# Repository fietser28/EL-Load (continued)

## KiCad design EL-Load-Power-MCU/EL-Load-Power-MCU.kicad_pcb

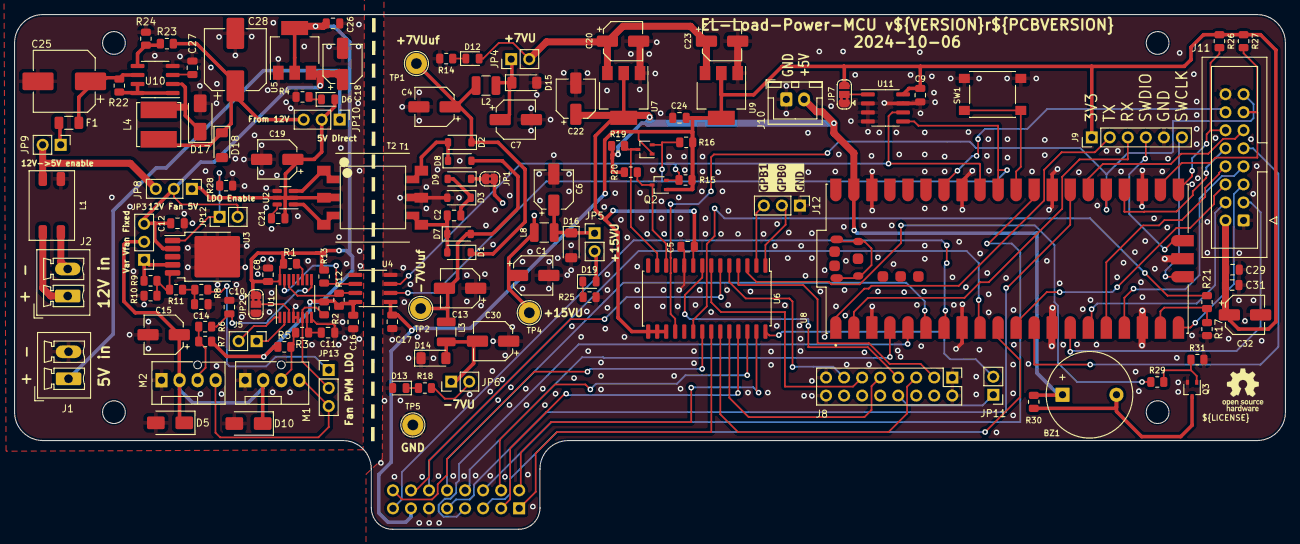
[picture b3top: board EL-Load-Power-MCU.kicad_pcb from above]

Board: 4 copper layers, 179.0 x 72.5 mm, 137 parts (1 on the bottom side), 108 nets.

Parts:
BZ1: Buzzer; Buzzer_12x9.5RM7.6
C1, C4, C6, C7, C13, C15, C18, C19, C20, C22, C23, C30, C32: 10u; CP_Elec_5x5.8
C2, C14, C29: 1u; C_0805_2012Metric
C5, C8, C9, C10, C11, C16, C17, C21, C31: 100n; C_0805_2012Metric
C12: 2.2u; C_0805_2012Metric
C24, C26: 10u; C_0805_2012Metric
C25, C28: 100u; CP_Elec_8x10.5
C27: 200p; C_0805_2012Metric
D1, D2, D3, D7, D8, D9: MBR0530; D_SOD-123
D5, D10, D17: SS14; D_SMA
D6, D12, D13, D19: LED; LED_0805_2012Metric
D14, D15: 16V; D_MiniMELF
D16: 20V; D_MiniMELF
D18: BZV55B5V6; D_MiniMELF
F1: 1A; Fuse_1206_3216Metric
H1, H2, H3, H4: MountingHole; MountingHole_3.2mm_M3_ISO14580
J1, J2: Conn_01x02; PhoenixContact_MCV_1,5_2-G-3.81_1x02_P3.81mm_Vertical
J5: PN sensor; PinHeader_1x02_P2.54mm_Vertical
J7, J8: PinHeader 2x08 P2.54mm; PinHeader_2x08_P2.54mm_Vertical
J9: SWD+UART header; PinHeader_1x06_P2.54mm_Vertical
J10: Power for serial interface; JST_XH_B2B-XH-A_1x02_P2.50mm_Vertical
J11: IDC-Header 2x08 P2.54mm; IDC-Header_2x08_P2.54mm_Vertical
J12: Conn_01x05_Pin; PinHeader_1x03_P2.54mm_Vertical
JP1: SolderJumper_2_Bridged; SolderJumper-2_P1.3mm_Bridged2Bar_RoundedPad1.0x1.5mm
JP2: I2C Address; SolderJumper-3_P1.3mm_Bridged2Bar12_RoundedPad1.0x1.5mm
JP3: Fan Volt/PWM; PinHeader_1x03_P2.54mm_Vertical
JP4, JP5, JP6, JP9: Jumper_2_Bridged; PinHeader_1x02_P2.54mm_Vertical
JP7: Jumper_3_Bridged12; SolderJumper-3_P1.3mm_Bridged2Bar12_RoundedPad1.0x1.5mm
JP8: Select Fan Voltage; PinHeader_1x03_P2.54mm_Vertical
JP10: Select 5V source; PinHeader_1x03_P2.54mm_Vertical
JP11: HW V3/V4; PinHeader_1x02_P2.54mm_Vertical
JP12: LDO En; PinHeader_1x02_P2.54mm_Vertical
JP13: PWM 2 LDO/PWM; PinHeader_1x03_P2.54mm_Vertical
L1: SRF0905-202Y; L_Bourns_SRF1260
L2, L3, L8: 10u; L_1210_3225Metric
L4: 100u / 300mA; L_Bourns_SRN6045TA
M1, M2: Fan_4pin; FanPinHeader_1x04_P2.54mm_Vertical
PCB1: Logo_Open_Hardware_Small; OSHW-Logo_5.7x6mm_SilkScreen
Q1, Q2, Q3: BSS138W; SOT-323_SC-70
R1, R2: 4k7; R_0805_2012Metric
R3, R6: 10; R_0805_2012Metric
R4, R14, R18, R21, R23, R28: 10k; R_0805_2012Metric
R5, R7, R8, R29, R30: 1k; R_0805_2012Metric
R9: 39k; R_0805_2012Metric
R10, R11, R24: 3k3; R_0805_2012Metric
R12, R13, R15, R16, R19, R20, R26, R27: 3k; R_0805_2012Metric
R17, R25, R31: 20k; R_0805_2012Metric
R22: 0.3; R_0805_2012Metric
SW1: Pico Reset; SW_Push_1P1T_NO_6x6mm_H9.5mm
T1: Wuerth_750315371; L_Wuerth_750315371
T2: Wuerth_750316031; L_Wuerth_750316031
TP1, TP2, TP4, TP5: TestPoint_Probe; TestPoint_Loop_D2.54mm_Drill1.5mm_Beaded
U1: MAX31760; QSOP-16_3.9x4.9mm_P0.635mm
U2: SN6505BDBV; SOT-23-6
U3: BD00FC0WFP-E2; TO-252-5_TabPin6
U4: Si8602AB; SOIC-8_3.9x4.9mm_P1.27mm
U5, U9: AMS1117-3.3; SOT-223-3_TabPin2
U6: MCP23017_SO; SOIC-28W_7.5x17.9mm_P1.27mm
U7: AZ1117-5.0; SOT-223-3_TabPin2
U8: SC0915; MODULE_SC0915
U10: MC34063AD; SOIC-8_3.9x4.9mm_P1.27mm
U11: 24C64; SOIC-8_3.9x4.9mm_P1.27mm
kibuzzard-66FFF99B: G***; kibuzzard-66FFF99B

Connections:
+3V3: C9.1, C17.2, C24.2, C29.1, C31.2, C32.1, J7.13, J9.1, J11.2, JP7.3 (B), Q1.1 (G), Q2.1 (G), R15.1, R16.1, R26.1, R27.1, U4.1 (AVDD), U9.2 (VO), U11.8 (VCC)
+3V3_ISO: C8.1, C16.2, C26.2, JP2.1 (A), R1.2, R2.1, R5.1, R7.1, R12.1, R13.1, U1.16 (VDD), U4.8 (BVDD), U5.2 (VO)
+5VD: BZ1.1 (-), C5.2, C22.1, J10.2, R19.1, R20.1, R30.1, U6.9 (VDD), U6.15 (A0), U6.16 (A1), U6.17 (A2), U7.2 (VO), U8.39 (VSYS)
+5V_ISO: C19.1, C21.2, D6.2 (A), JP8.1 (A), JP10.2 (C), T1.2 (N2-A), T2.2 (N2-A), U2.2 (VCC), U2.5 (EN)
+7VU: C20.1, C23.1, D12.2 (A), J8.4, J8.6, JP4.2 (B), U7.3 (VI), U9.3 (VI)
+12V_ISO: JP8.3 (B), JP9.2 (B), L1.3
+15VU: D19.2 (A), J8.10, JP5.2 (B)
+V_FANS: C12.1, C18.1, JP3.3 (B), JP8.2 (C), JP12.2 (B), U3.2 (Vcc), U5.3 (VI)
-7VU: J8.12, J8.14, JP6.2 (B), R18.2
/BLK: J11.7, U8.17 (GP13)
/CS1: J11.9, U8.12 (GP9)
/CS2: J11.10, U8.24 (GP18)
/DC: J11.6, U8.11 (GP8)
/Fan Controllers/Fan1PWM: JP13.3 (B), M1.4 (PWM), M2.4 (PWM)
/Fan Controllers/Fan1PWR: C15.1, D5.1 (K), D10.1 (K), JP3.2 (C), M1.2 (+), M2.2 (+)
/Fan Controllers/Fan1Tacho: M1.3 (Tacho), R3.2, R5.2
/Fan Controllers/Fan2Tacho: M2.3 (Tacho), R6.2, R7.2
/Fan Controllers/SCL_ISO: R13.2, U1.15 (SCL), U4.6 (BSCL)
/Fan Controllers/SDA_ISO: R12.2, U1.14 (SDA), U4.7 (BSDA)
/INT: J11.14, U8.34 (GP28)
/MCU/Buzzer: R29.1, U6.3 (GPB2)
/MCU/EL-ADC_CLK: J7.9, U8.27 (GP21)
/MCU/EL-ADC_CS: J7.6, U8.29 (GP22)
/MCU/EL-ADC_RDY: J7.5, U8.10 (GP7)
/MCU/EL-DAC1_CS: J7.12, U8.9 (GP6)
/MCU/EL-DAC2_CS: J7.15, U8.7 (GP5)
/MCU/EL-SPI_RX: J7.10, U8.6 (GP4)
/MCU/EL-SPI_SCK: J7.8, U8.4 (GP2)
/MCU/EL-SPI_TX: J7.7, U8.5 (GP3)
/MCU/HWGPIO_INT: R17.1, R21.2, U8.19 (GP14)
/MCU/HWIO_SCL: Q2.2 (S), R15.2, U4.3 (ASCL), U8.32 (GP27), U11.6 (SCL)
/MCU/HWIO_SDA: Q1.2 (S), R16.2, U4.2 (ASDA), U8.31 (GP26), U11.5 (SDA)
/MCU/HWProtEnable: J8.5, U6.23 (GPA2)
/MCU/OCPtriggered: J7.2, U6.27 (GPA6)
/MCU/OVPtriggered: J7.4, U6.26 (GPA5)
/MCU/RX: J9.3, U8.2 (GP1)
/MCU/TX: J9.2, U8.1 (GP0)
/MCU/VoltSenseClear: J8.3, U6.4 (GPB3)
/MCU/VoltSenseSet: J8.7, U6.8 (GPB7)
/MCU/clampOff: J7.3, U6.25 (GPA4)
/MCU/currRangeLow: J7.14, U6.6 (GPB5)
/MCU/resetProt: J7.1, U6.22 (GPA1)
/MCU/reversePolarity: JP11.2 (B), U6.28 (GPA7)
/MCU/senseError: J8.9, U6.24 (GPA3)
/MCU/voltRangeLow: J8.11, U6.7 (GPB6)
/MCU/~VonLatch: J8.13, U6.5 (GPB4)
/MCU/~Von: J7.16, U6.21 (GPA0)
/MISO: J11.8, U8.16 (GP12)
/MOSI: J11.4, U8.15 (GP11)
/PEN: J11.11, U8.26 (GP20)
/RESET: J11.5, U8.20 (GP15)
/SCLK: J11.3, U8.14 (GP10)
/Standalone Power/5Vout: C28.1, D18.1 (K), JP10.3 (B), L4.2, R23.1
/Standalone Power/12Vin: F1.1, JP9.1 (A)
/_KEYS_SCL: J11.13, R27.2, U8.22 (GP17)
/_KEYS_SDA: J11.12, R26.2, U8.21 (GP16)
/_reversePolarity: J8.8, JP11.1 (A)
/~RESET: J11.15, U6.18 (~RESET), U8.25 (GP19)
GND: C1.2, C4.2, C5.1, C6.2, C7.2, C9.2, C13.1, C17.1, C20.2, C22.2, C23.2, C24.1, C29.2, C30.1, C31.1, C32.2, D3.2 (A), D13.2 (A), D14.1 (K), D15.2 (A), D16.2 (A), J7.11, J8.1, J8.2, J8.15, J8.16, J9.5, J10.1, J11.1, J11.16, J12.1, JP7.1 (A), Q3.2 (S), R14.2, R17.2, R25.2, R31.2, SW1.2, T1.5 (N4-A), T2.5 (N4-A), TP5.1, U4.4 (AGND), U6.10 (VSS), U7.1 (GND), U8.3 (GND), U8.8 (GND), U8.13 (GND), U8.18 (GND), U8.23 (GND), U8.28 (GND), U8.33 (AGND), U8.38 (GND), U8.D2 (GND), U9.1 (GND), U11.2 (A1), U11.3 (A2), U11.4 (GND), U11.7 (WP)
GND_ISO: C8.2, C10.2, C11.2, C12.2, C14.2, C15.2, C16.1, C18.2, C19.2, C25.2, C26.1, C27.2, C28.2, D5.2 (A), D10.2 (A), D17.2 (A), D18.2 (A), J1.2, JP2.3 (B), L1.4, M1.1 (-), M2.1 (-), R4.2, R10.2, R24.2, R28.1, U1.4 (A1), U1.5 (A2), U1.8 (GND), U2.4 (GND), U3.6 (GND), U4.5 (BGND), U5.1 (GND), U10.4 (GND)
unnamed: BZ1.2 (+), Q3.3 (D), R30.2
unnamed: C14.1, R8.2, R11.2
unnamed: C2.2, D1.2 (A), D7.1 (K), T1.4 (N4-B), T2.4 (N4-B)
unnamed: C4.1, D1.1 (K), D2.1 (K), L2.2, TP1.1
unnamed: D2.2 (A), D8.1 (K), T1.6 (N3-A), T2.6 (N3-A)
unnamed: C2.1, D3.1 (K), D9.2 (A)
unnamed: D6.1 (K), R4.1
unnamed: C13.2, D7.2 (A), D8.2 (A), L3.2, TP2.1
unnamed: D9.1 (K), JP1.1 (A)
unnamed: D12.1 (K), R14.1
unnamed: D13.1 (K), R18.1
unnamed: C30.2, D14.2 (A), JP6.1 (A), L3.1
unnamed: C7.1, D15.1 (K), JP4.1 (A), L2.1
unnamed: C6.1, D16.1 (K), JP5.1 (A), L8.1
unnamed: D17.1 (K), L4.1, U10.2 (SwE)
unnamed: D19.1 (K), R25.1
unnamed: J1.1, JP10.1 (A)
unnamed: J2.1, L1.2
unnamed: J2.2, L1.1
unnamed: J5.1, U1.2 (DXN)
unnamed: J5.2, U1.1 (DXP)
unnamed: J9.4, U8.D3 (SWDIO)
unnamed: J9.6, U8.D1 (SWCLK)
unnamed: J12.2, U6.1 (GPB0)
unnamed: J12.3, U6.2 (GPB1)
unnamed: C1.1, JP1.2 (B), L8.2, TP4.1
unnamed: JP2.2 (C), U1.3 (A0)
unnamed: JP3.1 (A), R9.1, U3.4 (VOUT)
unnamed: JP7.2 (C), U11.1 (A0)
unnamed: JP12.1 (A), R28.2, U3.1 (EN)
unnamed: JP13.1 (A), R8.1
unnamed: JP13.2 (C), R2.2, U1.6 (PWM)
unnamed: Q1.3 (D), R19.2, U6.13 (SDA)
unnamed: Q2.3 (D), R20.2, U6.12 (SCK)
unnamed: Q3.1 (G), R29.2, R31.1
unnamed: T1.1 (N1-A), T2.1 (N1-A), U2.3 (D2)
unnamed: T1.3 (N2-B), T2.3 (N2-B), U2.1 (D1)
unnamed: C11.1, R3.1, U1.7 (TACH1)
unnamed: C10.1, R6.1, U1.9 (TACH2)
unnamed: R1.1, U1.11 (~SHDN)
unnamed: C21.1, U2.6 (CLK)
unnamed: R9.2, R10.1, R11.1, U3.5 (FB)
unnamed: R21.1, U6.20 (INTA)
unnamed: SW1.1, U8.30 (~RUN)
unnamed: R22.2, U10.1 (SwC), U10.7 (Ipk), U10.8 (DC)
unnamed: C27.1, U10.3 (TC)
unnamed: R23.2, R24.1, U10.5 (Vfb)
unnamed: C25.1, F1.2, R22.1, U10.6 (Vin)

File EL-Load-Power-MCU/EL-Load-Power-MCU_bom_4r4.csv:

Description,Footprint,Part,Reference,Value,Quantity,Datasheet,Part_Name,MPN,Consumable,Sim.Enable
"Buzzer, polarized",Buzzer_12x9.5RM7.6,Buzzer,BZ1,Buzzer,1,~,EM_Buzzer_single_5V_THT,,,
"Unpolarized capacitor, small symbol",C_0805_2012Metric,C_Small,C27,200p,1,~,C_200.0pF_0805_20%,,,
"Unpolarized capacitor, small symbol",C_0805_2012Metric,C_Small,C5 C8 C9 C10 C11 C16 C17 C21 C31,100n,9,~,C_100.0nF_50V_0805_10%_X7R,,,
"Unpolarized capacitor, small symbol",C_0805_2012Metric,C_Small,C2 C14 C29,1u,3,~,C_1.0uF_0805_20%,,,
"Unpolarized capacitor, small symbol",C_0805_2012Metric,C_Small,C12,2.2u,1,~,C_2.2uF_25V_X7R_10%_0805,,,
"Polarized capacitor, small symbol",CP_Elec_5x5.8,C_Polarized_Small,C1 C4 C6 C7 C13 C15 C18 C19 C20 C22 C23 C30 C32,10u,13,~,C_10uF_50V_Elec_5,EEE-FK1V470P,,
"Unpolarized capacitor, small symbol",C_0805_2012Metric,C_Small,C24 C26,10u,2,~,C_10.0uF_6V3_X7R_10%_0805,,,
Polarized capacitor,CP_Elec_8x10.5,C_Polarized,C25 C28,100u,2,~,C_100uF_50V_Elec_8,,,
"Zener diode, small symbol, filled shape",D_MiniMELF,D_Zener_Small_Filled,D14 D15,16V,2,~,D_Z_16V_miniMELF,,,
"Zener diode, small symbol, filled shape",D_MiniMELF,D_Zener_Small_Filled,D16,20V,1,~,D_Z_20V_miniMELF,,,
"5.6V, 500mW, 2%, Zener diode, MiniMELF",D_MiniMELF,BZV55B5V6,D18,BZV55B5V6,1,https://assets.nexperia.com/documents/data-sheet/BZV55_SER.pdf,D_Z_5V6_miniMELF,,,
Light emitting diode,LED_0805_2012Metric,LED,D6 D12 D13 D19,LED,4,~,D_LED_Groen_0805,,,
"30V 0.5A Schottky Power Rectifier Diode, SOD-123",D_SOD-123,MBR0530,D1 D2 D3 D7 D8 D9,MBR0530,6,http://www.mccsemi.com/up_pdf/MBR0520~MBR0580(SOD123).pdf,D_MBR0530T,MBR0530T1G,,
"Schottky diode, small symbol",D_SMA,D_Schottky_Small,D5 D10 D17,SS14,3,~,D_SS14,,,
"Resettable fuse, polymeric positive temperature coefficient",Fuse_1206_3216Metric,Polyfuse,F1,1A,1,~,F_SMD_PTC_1A_1206,,,
"Generic connector, single row, 01x02, script generated (kicad-library-utils/schlib/autogen/connector/)","PhoenixContact_MCV_1,5_2-G-3.81_1x02_P3.81mm_Vertical",Conn_01x02,J1 J2,Conn_01x02,2,~,H_Plug_2P_3.81MM_PCB_VERT,,,
"Generic connector, double row, 02x08, odd/even pin numbering scheme (row 1 odd numbers, row 2 even numbers), script generated (kicad-library-utils/schlib/autogen/connector/)",IDC-Header_2x08_P2.54mm_Vertical,Conn_02x08_Odd_Even,J11,IDC-Header 2x08 P2.54mm,1,~,H_IDC_2.54mm_Socket_THT_2x8pins,,,
"Generic connector, single row, 01x02, script generated (kicad-library-utils/schlib/autogen/connector/)",PinHeader_1x02_P2.54mm_Vertical,Conn_01x02,J5 J7 J8 J9 J12 JP3 JP4 JP5 JP6 JP8 JP9 JP10 JP11 JP12,PN sensor,14,~,H_Male_1x40_vertical_THT,,1,
"Generic connector, single row, 01x02, script generated (kicad-library-utils/schlib/autogen/connector/)",JST_XH_B2B-XH-A_1x02_P2.50mm_Vertical,Conn_01x02,J10,Power for serial interface,1,~,H_JST_XH_PCB_2P_VERT,,,
"Inductor with ferrite core, small symbol",L_1210_3225Metric,L_Ferrite_Small,L2 L3 L8,10u ,3,https://product.tdk.com/system/files/dam/doc/product/inducto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,L_10uH_480mohm_450mA_,NLCV32T-100K-EF,,
Inductor,L_Bourns_SRN6045TA,L,L4,100u / 300mA,1,~,L_100uH_CD54,,,
Coupled inductor with ferrite core,L_Bourns_SRF1260,L_Ferrite_Coupled_1423,L1,SRF0905-202Y,1,~,LC_2000uH_0.6A_0905,SRF0905-202Y,,
"Fan, tacho output, PWM input, 4-pin connector",FanPinHeader_1x04_P2.54mm_Vertical,Fan_4pin,M1 M2,Fan_4pin,2,http://www.formfactors.org/developer%5Cspecs%5Crev1_2_public.pdf,H_Molex_47053-1000_THT_PC_Fan,,,
"Open Hardware logo, small",OSHW-Logo_5.7x6mm_SilkScreen,Logo_Open_Hardware_Small,PCB1,Logo_Open_Hardware_Small,1,~,PCB_EL-Load-Power-MCU,,,0
"50V Vds, 0.22A Id, N-Channel MOSFET, SOT-23",SOT-323_SC-70,BSS138,Q1 Q2 Q3,BSS138W,3,https://www.diodes.com/assets/Datasheets/BSS138W.pdf,Q_BSS138W,,,
"Resistor, small symbol",R_0805_2012Metric,R_Small,R22,0.3,1,~,R_0.33Ω_0805_1%,,,
"Resistor, small symbol",R_0805_2012Metric,R_Small,R3 R6,10,2,~,R_10.0Ω_0805_1%,,,
"Resistor, small symbol",R_0805_2012Metric,R_Small,R5 R7 R8 R29 R30,1k,5,~,R_1.0kΩ_0805_1%,,,
"Resistor, small symbol",R_0805_2012Metric,R_Small,R12 R13 R15 R16 R19 R20 R26 R27,3k,8,~,R_3.0kΩ_0805_1%,,,
"Resistor, small symbol",R_0805_2012Metric,R_Small,R10 R11 R24,3k3,3,~,R_3.3kΩ_0805_1%,,,
"Resistor, small symbol",R_0805_2012Metric,R_Small,R1 R2,4k7,2,~,R_4.7kΩ_0805_1%,,,
"Resistor, small symbol",R_0805_2012Metric,R_Small,R4 R14 R18 R21 R23 R28,10k,6,~,R_10.0kΩ_0805_1%,,,
"Resistor, small symbol",R_0805_2012Metric,R_Small,R17 R25 R31,20k,3,~,R_20.0kΩ_0805_1%,,,
"Resistor, small symbol",R_0805_2012Metric,R_Small,R9,39k,1,~,R_39.0kΩ_0805_1%,,,
"Push button switch, generic, two pins",SW_Push_1P1T_NO_6x6mm_H9.5mm,SW_Push,SW1,Pico Reset,1,~,SW_SPST_NO_SMD_6x6x5mm,,,
"Transformer, dual primary, dual secondary",L_Wuerth_750316031,Transformer_2P_2S,T2,Wuerth_750316031,1,~,T_1:1:1.75:1.75_185uH_SMD,,,
"I2C Serial EEPROM, 64Kb, DIP-8/SOIC-8/TSSOP-8/DFN-8",SOIC-8_3.9x4.9mm_P1.27mm,24LC64,U11,24C64,1,http://ww1.microchip.com/downloads/en/DeviceDoc/21189f.pdf,U_24C64,,,
"1A Low Dropout regulator, positive, 3.3V fixed output, SOT-223",SOT-223-3_TabPin2,AMS1117-3.3,U5 U9,AMS1117-3.3,2,http://www.advanced-monolithic.com/pdf/ds1117.pdf,U_AMS1117-3.3,,,
"1A 20V Fixed LDO Linear Regulator, 5.0V, SOT-89/SOT-223/TO-220/TO-252/TO-263",SOT-223-3_TabPin2,AZ1117-5.0,U7,AZ1117-5.0,1,https://www.diodes.com/assets/Datasheets/AZ1117.pdf,U_AZ1117CH-5.0TRG1,,,
"1.5A low dropout linear regulator, adjustable output, TO-252",TO-252-5_TabPin6,BD00FC0W,U3,BD00FC0WFP-E2,1,,U_BD00FC0WFP,,,
"Precision Fan-Speed Controller with Nonvolatile Lookup Table, I2C, SOIC-16",QSOP-16_3.9x4.9mm_P0.635mm,MAX31760,U1,MAX31760,1,,U_MAX31760AEE+T,,,
"1.5A, step-up/down/inverting switching regulator, 3-40V Vin, 100kHz, SO-8",SOIC-8_3.9x4.9mm_P1.27mm,MC34063AD,U10,MC34063AD,1,http://www.onsemi.com/pub_link/Collateral/MC34063A-D.PDF,U_MC34063AD,,,
"16-bit I/O expander, I2C, interrupts, w pull-ups, SOIC-28",SOIC-28W_7.5x17.9mm_P1.27mm,MCP23017_SO,U6,MCP23017_SO,1,http://ww1.microchip.com/downloads/en/DeviceDoc/20001952C.pdf,U_MCP23017-E/SO,,,
Raspberry Pi Pico Embedded Dev Module | Raspberry Pi SC0915,MODULE_SC0915,SC0915,U8,SC0915,1,,EM_Raspberry_Pi_Pico,SC0915,,
"Low Noise, 1A, Transformer Drivers for Isolated Power Supplies, 420 kHz, SOT-23-6",SOT-23-6,SN6505BDBV,U2,SN6505BDBV,1,http://www.ti.com/lit/ds/symlink/sn6505b.pdf,U_SN6505BDBVT_SOT-23-6,,,
,SOIC-8_3.9x4.9mm_P1.27mm,Si8602AD,U4,Si8602AB,1,,U_SI8602AB-B-IS,,,





Component Groups:,46
Component Count:,123
Fitted Components:,123
Number of PCBs:,1
Total components:,123
Schematic Version:,4r4
Schematic Date:,2024-09-14
PCB Variant:,default
BoM Date:,2024-09-14
Schematic Source:,EL-Load-Power-MCU.kicad_sch
KiCad Version:,Eeschema 7.0.9

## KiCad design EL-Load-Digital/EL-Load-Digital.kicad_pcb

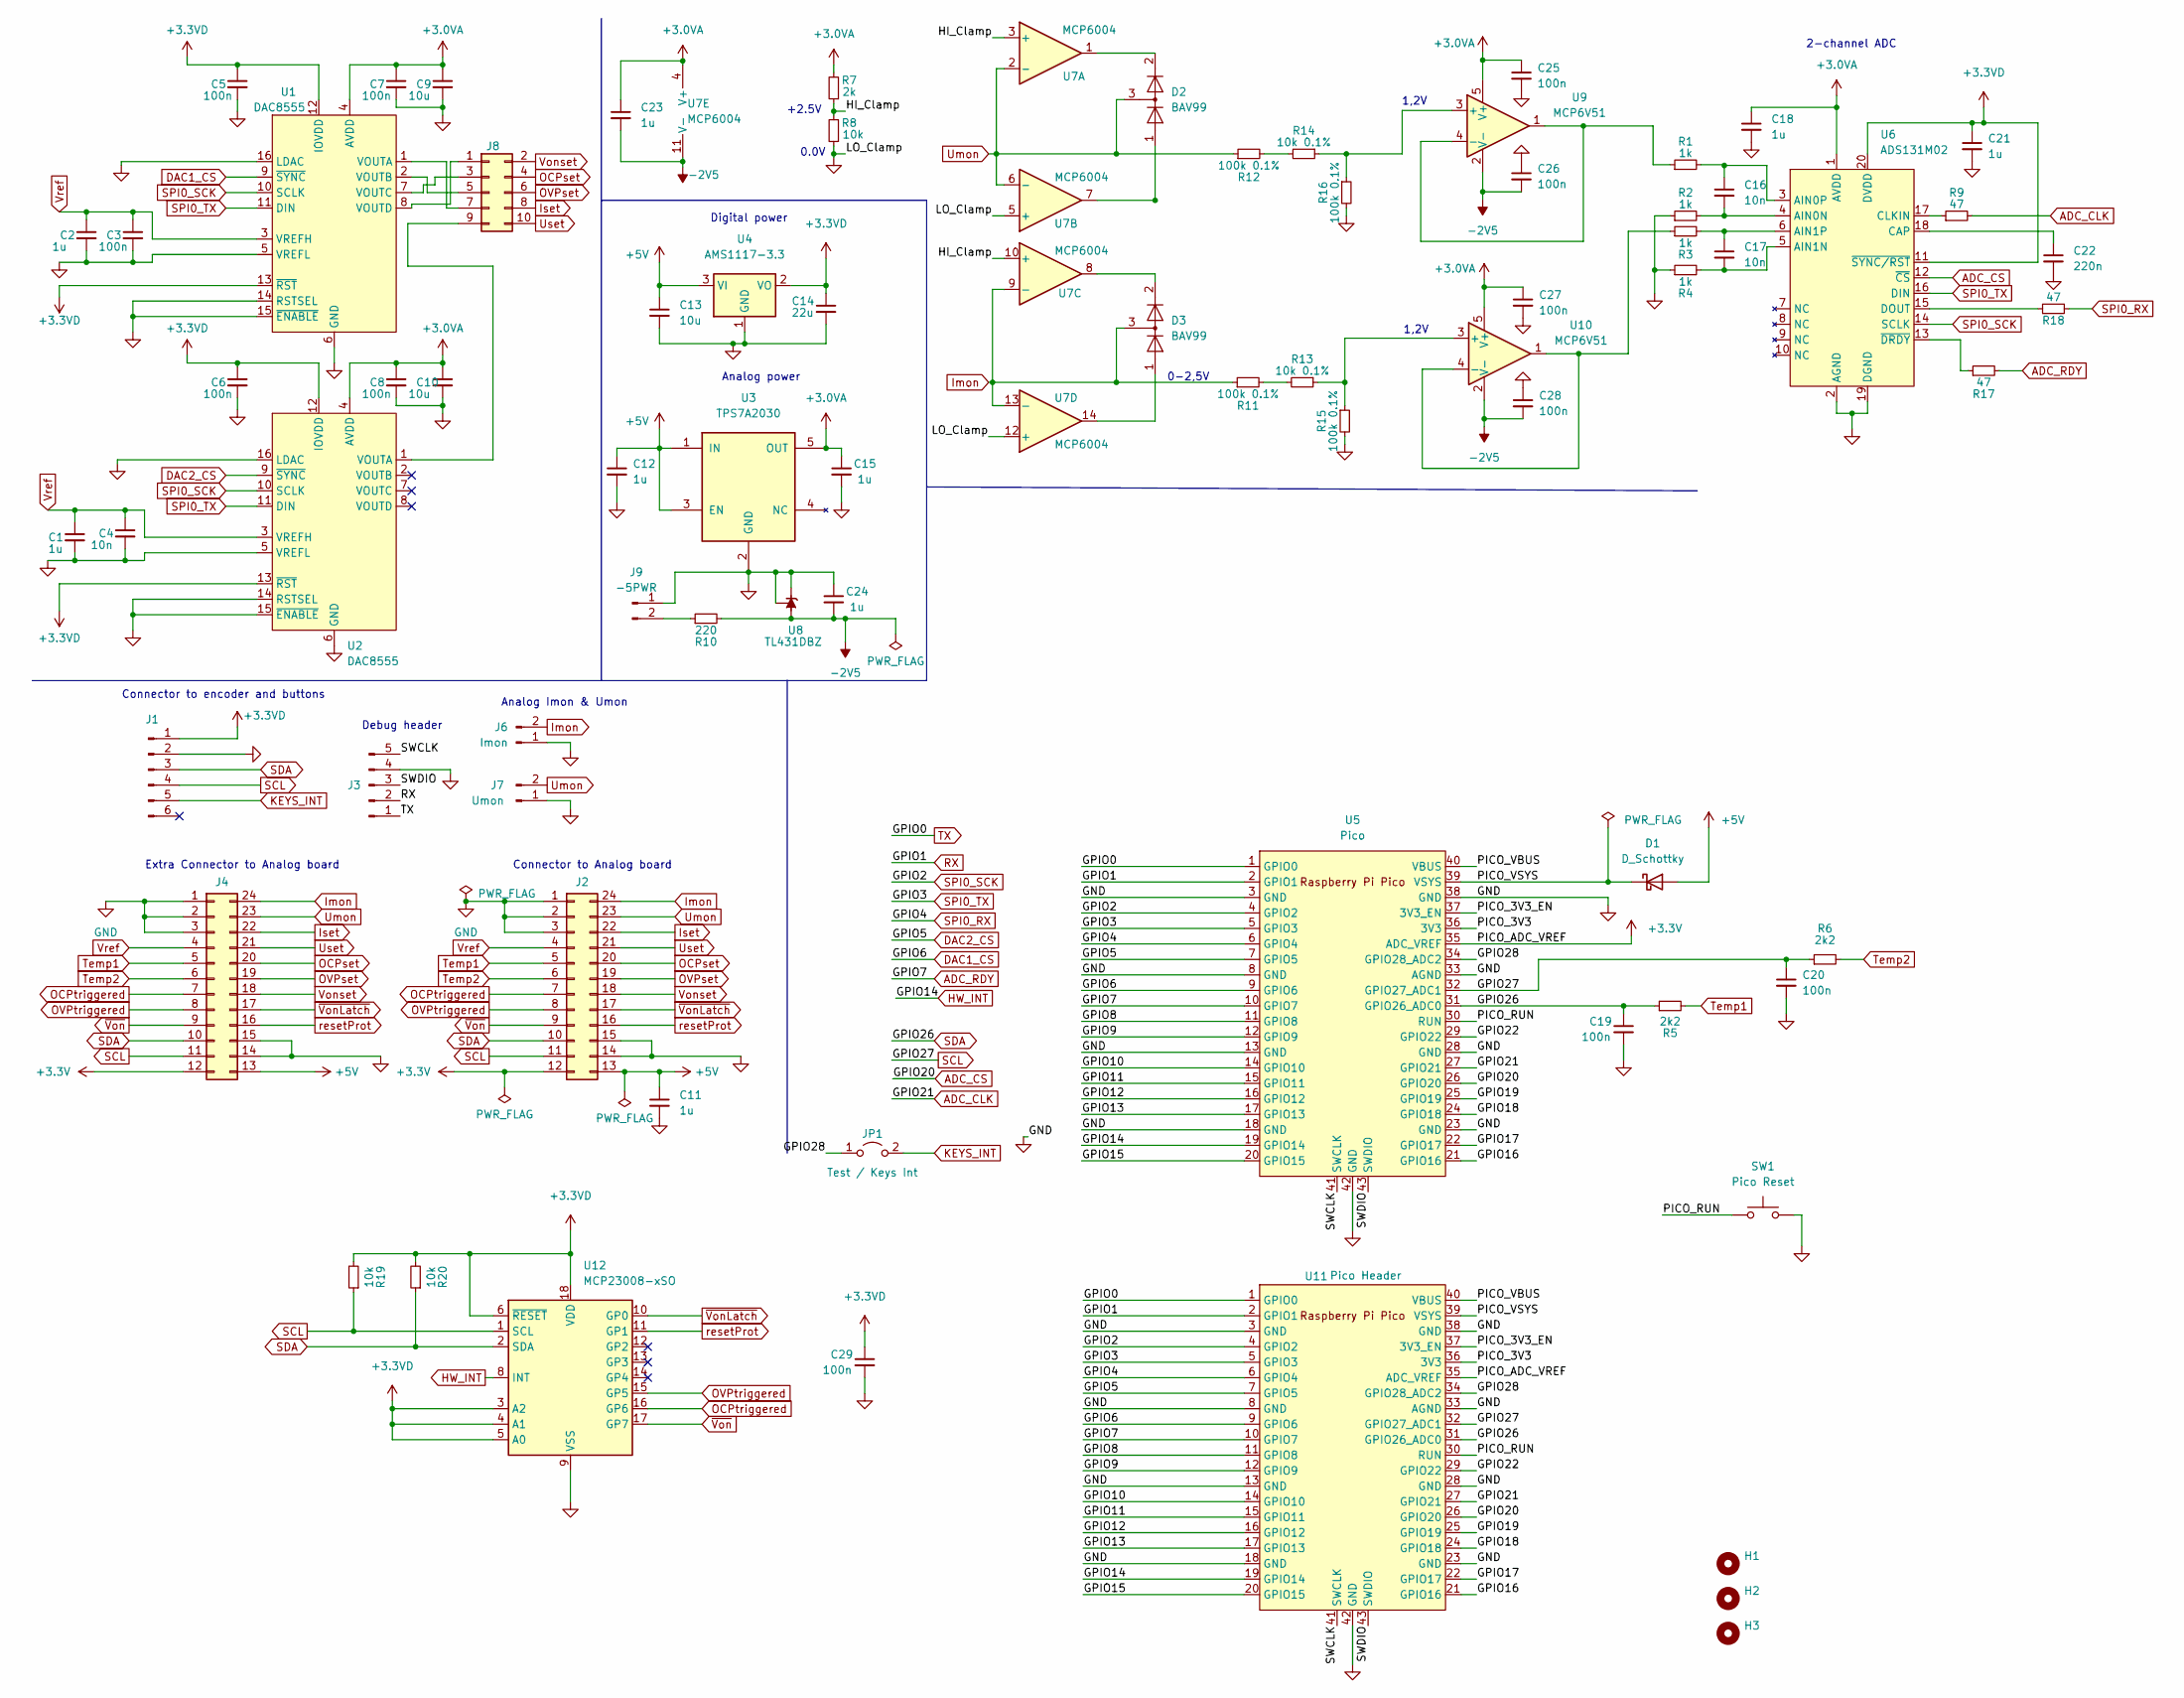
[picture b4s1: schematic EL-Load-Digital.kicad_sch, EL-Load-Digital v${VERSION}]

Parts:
C1, C2, C11, C12, C15, C18, C21, C23, C24: 1u; C_0805_2012Metric_Pad1.18x1.45mm_HandSolder
C3, C5, C6, C7, C8, C19, C20, C25, C26, C27, C28, C29: 100n; C_0805_2012Metric_Pad1.18x1.45mm_HandSolder
C4, C16, C17: 10n; C_0805_2012Metric_Pad1.18x1.45mm_HandSolder
C9, C10, C13: 10u; C_0805_2012Metric_Pad1.18x1.45mm_HandSolder
C14: 22u; C_0805_2012Metric_Pad1.18x1.45mm_HandSolder
C22: 220n; C_0805_2012Metric_Pad1.18x1.45mm_HandSolder
D1: D_Schottky; D_SMA_Handsoldering
D2, D3: BAV99; SOT-23
H1, H2, H3: MountingHole; MountingHole_2.7mm_M2.5_Pad_Via
J1: Conn_01x06_Male; JST_PH_S6B-PH-SM4-TB_1x06-1MP_P2.00mm_Horizontal
J2: Conn_02x12_Counter_Clockwise; PinSocket_2x12_P2.54mm_Vertical
J3: Conn_01x05_Male; PinHeader_1x05_P2.54mm_Vertical
J4: Conn_02x12_Counter_Clockwise; PinHeader_2x12_P2.54mm_Vertical
J6: Imon; PhoenixContact_MCV_1,5_2-G-3.81_1x02_P3.81mm_Vertical
J7: Umon; PhoenixContact_MCV_1,5_2-G-3.81_1x02_P3.81mm_Vertical
J8: Conn_02x05_Odd_Even; PinHeader_2x05_P2.54mm_Vertical
J9: -5PWR; JST_XH_B2B-XH-A_1x02_P2.50mm_Vertical
JP1: Test / Keys Int; PinHeader_1x02_P2.54mm_Vertical
R1, R2, R3, R4: 1k; R_0805_2012Metric_Pad1.20x1.40mm_HandSolder
R5, R6: 2k2; R_0805_2012Metric_Pad1.20x1.40mm_HandSolder
R7: 2k; R_0805_2012Metric_Pad1.20x1.40mm_HandSolder
R8, R19, R20: 10k; R_0805_2012Metric_Pad1.20x1.40mm_HandSolder
R9, R17, R18: 47; R_0805_2012Metric_Pad1.20x1.40mm_HandSolder
R10: 220; R_0805_2012Metric_Pad1.20x1.40mm_HandSolder
R11, R12, R15, R16: 100k 0.1%; R_0805_2012Metric_Pad1.20x1.40mm_HandSolder
R13, R14: 10k 0.1%; R_0805_2012Metric_Pad1.20x1.40mm_HandSolder
SW1: Pico Reset; SW_Push_1P1T_NO_6x6mm_H9.5mm
U1, U2: DAC8555; TSSOP-16_4.4x5mm_P0.65mm
U3: TPS7A2030; SOT-23-5_HandSoldering
U4: AMS1117-3.3; SOT-223-3_TabPin2
U5: Pico; RPi_Pico_SMD_TH
U6: ADS131M02; TSSOP-20_4.4x6.5mm_P0.65mm
U7: MCP6004; SOIC-14_3.9x8.7mm_P1.27mm
U8: TL431DBZ; SOT-23
U9, U10: MCP6V51; SOT-23-5
U11: Pico Header; RPi_Pico_REVERSED_HEADER_SMD_TH
U12: MCP23008-xSO; SOIC-18W_7.5x11.6mm_P1.27mm

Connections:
+3.0VA: C7.1, C8.1, C9.1, C10.1, C15.1, C18.1, C23.1, C25.1, C27.1, R7.2, U1.4 (AVDD), U2.4 (AVDD), U3.5 (OUT), U6.1 (AVDD), U7.4 (V+), U9.5 (V+), U10.5 (V+)
+3.3V: J2.12, J4.12, U5.35 (ADC_VREF), U11.35 (ADC_VREF)
+3.3VD: C5.1, C6.1, C14.1, C21.1, C29.1, J1.1, R19.2, R20.2, U1.12 (IOVDD), U1.13 (~RST), U2.12 (IOVDD), U2.13 (~RST), U4.2 (VO), U6.11 (~SYNC/RST), U6.20 (DVDD), U12.3 (A2), U12.4 (A1), U12.5 (A0), U12.6 (~RESET), U12.18 (VDD); also elsewhere on the board
+5V: C11.1, C12.1, C13.1, D1.2 (A), J2.13, J4.13, U3.1 (IN), U3.3 (EN), U4.3 (VI)
-2V5: C23.2, C24.2, C26.2, C28.2, R10.2, U7.11 (V-), U8.3 (A), U9.2 (V-), U10.2 (V-)
/GPIO8: U5.11 (GPIO8), U11.11 (GPIO8)
/GPIO9: U5.12 (GPIO9), U11.12 (GPIO9)
/GPIO10: U5.14 (GPIO10), U11.14 (GPIO10)
/GPIO11: U5.15 (GPIO11), U11.15 (GPIO11)
/GPIO12: U5.16 (GPIO12), U11.16 (GPIO12)
/GPIO13: U5.17 (GPIO13), U11.17 (GPIO13)
/GPIO15: U5.20 (GPIO15), U11.20 (GPIO15)
/GPIO16: U5.21 (GPIO16), U11.21 (GPIO16)
/GPIO17: U5.22 (GPIO17), U11.22 (GPIO17)
/GPIO18: U5.24 (GPIO18), U11.24 (GPIO18)
/GPIO19: U5.25 (GPIO19), U11.25 (GPIO19)
/GPIO22: U5.29 (GPIO22), U11.29 (GPIO22)
/GPIO28: JP1.1 (A), U5.34 (GPIO28_ADC2), U11.34 (GPIO28_ADC2)
/HI_Clamp: R7.1, R8.2, U7.3 (+), U7.10 (+)
/PICO_3V3: U5.36 (3V3), U11.36 (3V3)
/PICO_3V3_EN: U5.37 (3V3_EN), U11.37 (3V3_EN)
/PICO_RUN: SW1.1, U5.30 (RUN), U11.30 (RUN)
/PICO_VBUS: U5.40 (VBUS), U11.40 (VBUS)
/PICO_VSYS: D1.1 (K), U5.39 (VSYS), U11.39 (VSYS)
/SWCLK: J3.5, U5.41 (SWCLK), U11.41 (SWCLK)
/SWDIO: J3.3, U5.43 (SWDIO), U11.43 (SWDIO)
ADC_CLK: R9.2, U5.27 (GPIO21), U11.27 (GPIO21)
ADC_CS: U5.26 (GPIO20), U6.12 (~CS), U11.26 (GPIO20)
ADC_RDY: R17.2, U5.10 (GPIO7), U11.10 (GPIO7)
DAC1_CS: U1.9 (~SYNC), U5.9 (GPIO6), U11.9 (GPIO6)
DAC2_CS: U2.9 (~SYNC), U5.7 (GPIO5), U11.7 (GPIO5)
GP2: U12.12 (GP2); also elsewhere on the board
GP3: U12.13 (GP3); also elsewhere on the board
HW_INT: U5.19 (GPIO14), U11.19 (GPIO14), U12.8 (INT)
Imon: D3.3 (K), J2.24, J4.24, J6.2, R11.1, U7.9 (-), U7.13 (-)
Iset: J2.22, J4.22, J8.8
KEYS_INT: J1.5, JP1.2 (B)
unnamed: D2.2 (A), U7.1
unnamed: D2.1 (K), U7.7
unnamed: D3.2 (A), U7.8
unnamed: D3.1 (K), U7.14
unnamed: J8.1, U1.8 (VOUTD)
unnamed: J8.3, U1.7 (VOUTC)
unnamed: J8.5, U1.2 (VOUTB)
unnamed: J8.7, U1.1 (VOUTA)
unnamed: J8.9, U2.1 (VOUTA)
unnamed: J9.2, R10.1
unnamed: R11.2, R13.2
unnamed: R12.2, R14.2
unnamed: C16.2, R2.2, U6.4 (AIN0N)
unnamed: C16.1, R1.2, U6.3 (AIN0P)
unnamed: C17.2, R4.2, U6.5 (AIN1N)
unnamed: C17.1, R3.2, U6.6 (AIN1P)
unnamed: C22.1, U6.18 (CAP)
unnamed: R9.1, U6.17 (CLKIN)
unnamed: R18.1, U6.15 (DOUT)
unnamed: R17.1, U6.13 (~DRDY)
unnamed: R14.1, R16.1, U9.3 (+)
unnamed: R1.1, U9.1, U9.4 (-)
unnamed: R13.1, R15.1, U10.3 (+)
unnamed: R3.1, U10.1, U10.4 (-)
OCPset: J2.20, J4.20, J8.4
OCPtriggered: J2.7, J4.7, U12.16 (GP6)
OVPset: J2.19, J4.19, J8.6
OVPtriggered: J2.8, J4.8, U12.15 (GP5)
RX: J3.2, U5.2 (GPIO1), U11.2 (GPIO1)
SCL: C20.1, J1.4, J2.11, J4.11, R6.1, R19.1, U5.32 (GPIO27_ADC1), U11.32 (GPIO27_ADC1), U12.1 (SCL); also elsewhere on the board
SDA: C19.1, J1.3, J2.10, J4.10, R5.1, R20.1, U5.31 (GPIO26_ADC0), U11.31 (GPIO26_ADC0), U12.2 (SDA); also elsewhere on the board
SPI0_RX: R18.2, U5.6 (GPIO4), U11.6 (GPIO4)
SPI0_SCK: U1.10 (SCLK), U2.10 (SCLK), U5.4 (GPIO2), U6.14 (SCLK), U11.4 (GPIO2)
SPI0_TX: U1.11 (DIN), U2.11 (DIN), U5.5 (GPIO3), U6.16 (DIN), U11.5 (GPIO3)
TX: J3.1, U5.1 (GPIO0), U11.1 (GPIO0)
Temp1: J2.5, J4.5, R5.2
Temp2: J2.6, J4.6, R6.2
Umon: D2.3 (K), J2.23, J4.23, J7.2, R12.1, U7.2 (-), U7.6 (-)
Uset: J2.21, J4.21, J8.10
Vonset: J2.18, J4.18, J8.2
Vref: C1.1, C2.1, C3.1, C4.1, J2.4, J4.4, U1.3 (VREFH), U2.3 (VREFH)
resetProt: J2.16, J4.16, U12.11 (GP1)
~VonLatch: J2.17, J4.17, U12.10 (GP0)
~Von: J2.9, J4.9, U12.17 (GP7)

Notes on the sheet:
0.0V
Digital power
Connector to encoder and buttons
Debug header
Analog power
0-2,5V
+2.5V
2-channel ADC
Analog Imon & Umon
Extra Connector to Analog board
1,2V
Connector to Analog board

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
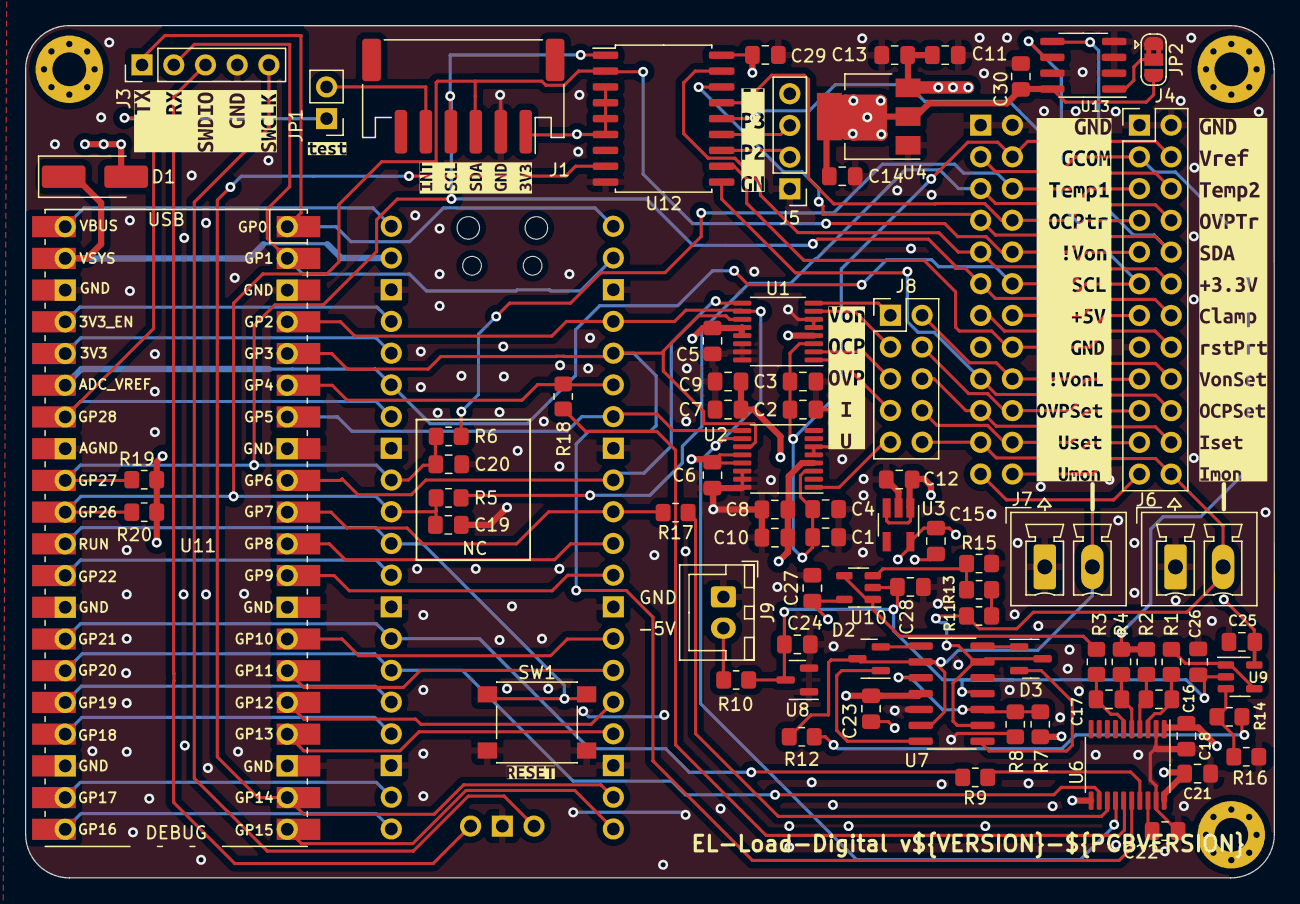
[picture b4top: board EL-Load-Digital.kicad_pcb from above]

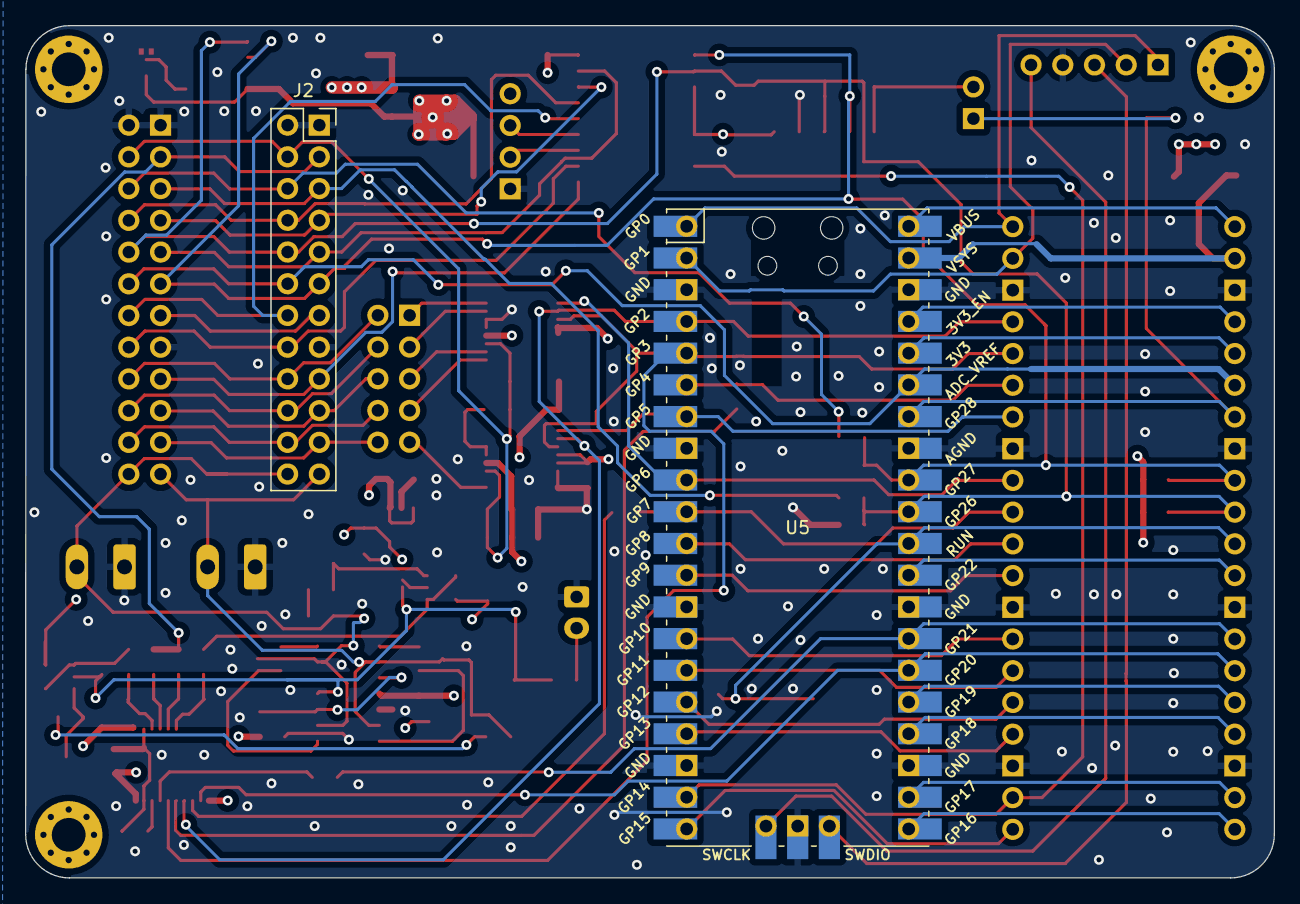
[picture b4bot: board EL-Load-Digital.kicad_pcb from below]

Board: 4 copper layers, 100.0 x 68.2 mm, 89 parts (2 on the bottom side), 85 nets.

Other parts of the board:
C30: 100n; C_0805_2012Metric_Pad1.18x1.45mm_HandSolder
J5: Conn_01x04_Pin; PinHeader_1x04_P2.54mm_Vertical
JP2: Jumper_3_Bridged12; SolderJumper-3_P1.3mm_Bridged2Bar12_RoundedPad1.0x1.5mm
U13: 24LC64; SOIC-8_3.9x4.9mm_P1.27mm
kibuzzard-63C41D86: G***; kibuzzard-63C41D86
kibuzzard-63C41DE1: G***; kibuzzard-63C41DE1
kibuzzard-64AAE6E2: G***; kibuzzard-64AAE6E2
kibuzzard-64AAEA42: G***; kibuzzard-64AAEA42
kibuzzard-64B1211E: G***; kibuzzard-64B1211E
kibuzzard-64B12145: G***; kibuzzard-64B12145
kibuzzard-635D1A4A: G***; kibuzzard-635D1A4A
kibuzzard-6429B73A: G***; kibuzzard-6429B73A

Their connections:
+3.3VD: C30.1, JP2.3 (B), U13.8 (VCC); also elsewhere on the board
GP2: J5.2; also elsewhere on the board
GP3: J5.3; also elsewhere on the board
unnamed: JP2.2 (C), U13.1 (A0)
SCL: U13.6 (SCL); also elsewhere on the board
SDA: U13.5 (SDA); also elsewhere on the board

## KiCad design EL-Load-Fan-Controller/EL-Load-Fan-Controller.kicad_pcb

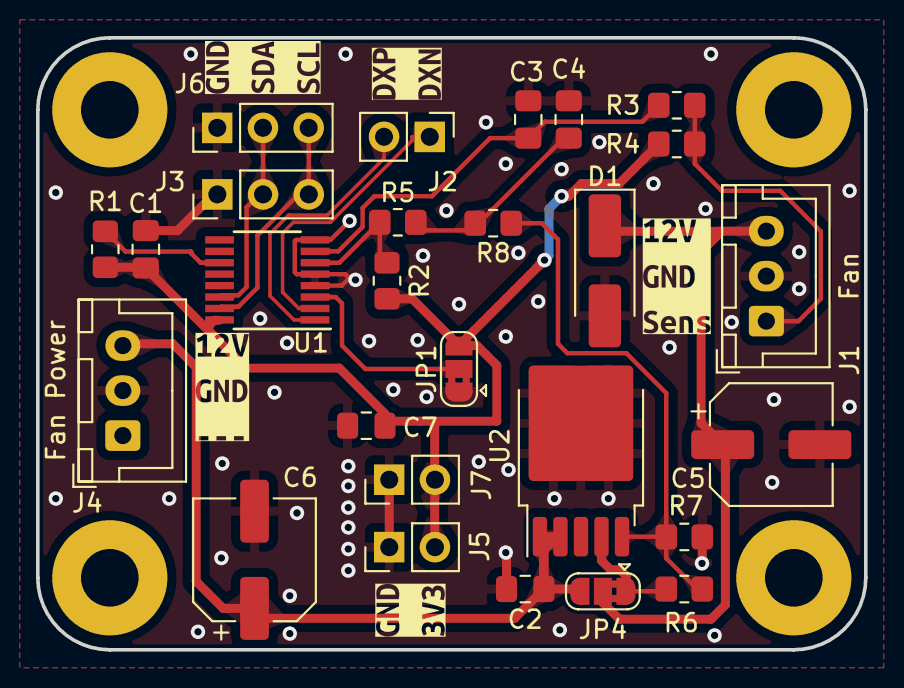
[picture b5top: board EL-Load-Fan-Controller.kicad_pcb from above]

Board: 2 copper layers, 46.0 x 34.0 mm, 36 parts (0 on the bottom side), 16 nets.

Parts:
C1, C3: 100n; C_0805_2012Metric_Pad1.18x1.45mm_HandSolder
C2: 10n; C_0805_2012Metric_Pad1.18x1.45mm_HandSolder
C4, C7: 1u; C_0805_2012Metric_Pad1.18x1.45mm_HandSolder
C5, C6: 10u; CP_Elec_6.3x5.8
D1: SS14; D_SMA_Handsoldering
H1, H2, H3, H4: MountingHole; MountingHole_3.2mm_M3_Pad
J1: Fan; JST_XH_B3B-XH-A_1x03_P2.50mm_Vertical
J2: PN sensor; PinHeader_1x02_P2.54mm_Vertical
J3, J6: I2C; PinHeader_1x03_P2.54mm_Vertical
J4: Fan Power; JST_XH_B3B-XH-A_1x03_P2.50mm_Vertical
J5, J7: 3V3; PinHeader_1x02_P2.54mm_Vertical
JP1: I2C Address; SolderJumper-3_P1.3mm_Bridged2Bar12_RoundedPad1.0x1.5mm
JP4: SolderJumper_3_Bridged12; SolderJumper-3_P1.3mm_Bridged2Bar12_RoundedPad1.0x1.5mm
R1, R2: 4k7; R_0805_2012Metric_Pad1.20x1.40mm_HandSolder
R3: 10; R_0805_2012Metric_Pad1.20x1.40mm_HandSolder
R4, R5: 1k; R_0805_2012Metric_Pad1.20x1.40mm_HandSolder
R6: 39k; R_0805_2012Metric_Pad1.20x1.40mm_HandSolder
R7, R8: 3k3; R_0805_2012Metric_Pad1.20x1.40mm_HandSolder
U1: MAX31760; QSOP-16_3.9x4.9mm_P0.635mm
U2: BD00FC0WFP-E2; TO-252-5_TabPin6
kibuzzard-64B07B9D: G***; kibuzzard-64B07B9D
kibuzzard-64B073D4: G***; kibuzzard-64B073D4
kibuzzard-64B07534: G***; kibuzzard-64B07534
kibuzzard-64B10700: G***; kibuzzard-64B10700
kibuzzard-64B16975: G***; kibuzzard-64B16975

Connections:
+3.3V: C1.1, C7.1, J5.2, J7.2, JP1.3 (B), R1.2, R2.1, R4.1, U1.16 (VDD)
+12P: C2.1, C6.1, J4.3, JP4.3 (B), U2.1 (EN), U2.2 (Vcc)
/DXN: J2.1, U1.2 (DXN)
/DXP: J2.2, U1.1 (DXP)
/FanPWR: C5.1, D1.1 (K), J1.3, JP4.2 (C)
/Tacho: J1.1, R3.2, R4.2
GND: C1.2, C2.2, C3.2, C4.2, C5.2, C6.2, C7.2, D1.2 (A), J1.2, J3.1, J4.2, J5.1, J6.1, J7.1, JP1.1 (A), R7.2, U1.4 (A1), U1.5 (A2), U1.8 (GND), U2.6 (GND)
unnamed: C4.1, R5.2, R8.2
unnamed: JP1.2 (C), U1.3 (A0)
unnamed: JP4.1 (A), R6.1, U2.4 (VOUT)
unnamed: R2.2, R5.1, U1.6 (PWM)
unnamed: C3.1, R3.1, U1.7 (TACH1)
unnamed: R1.1, U1.11 (~SHDN)
unnamed: R6.2, R7.1, R8.1, U2.5 (FB)
SCL: J3.3, J6.3, U1.15 (SCL)
SDA: J3.2, J6.2, U1.14 (SDA)

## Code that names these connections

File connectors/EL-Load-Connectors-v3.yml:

connectors:
    MCU-J8:
        type: PinHeader 2x08 P2.54mm
        pins: [1, 2, 3, 4, 5, 6, 7, 8, 9, 10, 11, 12, 13, 14, 15, 16, ]
        pinlabels: [GND, GND, MCU/VoltSenseClear, +7VU, MCU/HWProtEnable, +7VU, MCU/VoltSenseSet, _reversePolarity, MCU/senseError, +15VU, MCU/voltRangeLow, -7VU, MCU/~VonLatch, -7VU, GND, GND, ]

    MCU-J7:
        type: PinHeader 2x08 P2.54mm
        pins: [1, 2, 3, 4, 5, 6, 7, 8, 9, 10, 11, 12, 13, 14, 15, 16, ]
        pinlabels: [MCU/resetProt, MCU/OCPtriggered, MCU/clampOff, MCU/OVPtriggered, MCU/EL-ADC_RDY, MCU/EL-ADC_CS, MCU/EL-SPI_TX, MCU/EL-SPI_SCK, MCU/EL-ADC_CLK, MCU/EL-SPI_RX, GND, MCU/EL-DAC1_CS, +3V3, MCU/currRangeLow, MCU/EL-DAC2_CS, MCU/~Von, ]

    MCU-J11:
        type: IDC-Header 2x08 P2.54mm
        pins: [1, 2, 3, 4, 5, 6, 7, 8, 9, 10, 11, 12, 13, 14, 15, 16, ]
        pinlabels: [GND, +3V3, SCLK, MOSI, RESET, DC, BLK, MISO, CS1, CS2, PEN, _KEYS_SDA, _KEYS_SCL, INT, ~RESET, GND, ]

    Panel-J2:
        type: Conn_02x08_Odd_Even
        pins: [1, 2, 3, 4, 5, 6, 7, 8, 9, 10, 11, 12, 13, 14, 15, 16, ]
        pinlabels: [GND, +3V3, SCLK, MOSI, RESET, DC, BLK, MISO, CS1, CS2, PEN, SDA, SCL, INT, ~RESET, GND, ]

    Analog-J8:
        type: Conn_02x08_Odd_Even
        pins: [1, 2, 3, 4, 5, 6, 7, 8, 9, 10, 11, 12, 13, 14, 15, 16, ]
        pinlabels: [resetProt, OCPtriggered, ClampOff, OVPtriggered, ADC_RDY, ADC_CS, SPI0_TX, SPI0_SCK, ADC_CLK, SPI0_RX, GND, DAC1_CS, +3.3VD, CurrRangeLow, DAC2_CS, ~Von, ]

    Analog-J4:
        type: Conn_02x08_Odd_Even
        pins: [1, 2, 3, 4, 5, 6, 7, 8, 9, 10, 11, 12, 13, 14, 15, 16, ]
        pinlabels: [GND, GND, VsenseClear, +6V, HWProtEnable, +6V, VsenseSet, +15V, SenseError, +15V, VoltRangeLow, -6V, ~VonLatch, -6V, GND, GND, ]

cables:
  W1:
    gauge: 28 AWG
    length: 0.045
    color_code: DIN
    wirecount: 16
    shield: false

  W2:
    gauge: 28 AWG
    length: 0.05
    color_code: DIN
    wirecount: 16
    shield: false

connections:
  -
    - MCU-J8: [1,2,3,4,5,6,7,8,9,10,11,12,13,14,15,16,]
    - W1: [1,2,3,4,5,6,7,8,9,10,11,12,13,14,15,16,]
    - Analog-J4: [1,2,3,4,5,6,7,8,9,10,11,12,13,14,15,16,]
  -
    - MCU-J7: [1,2,3,4,5,6,7,8,9,10,11,12,13,14,15,16,]
    - [ -,-,-,-,-,-,-,-,-,-,-,-,-,-,-,-, ]
    - Analog-J8: [1,2,3,4,5,6,7,8,9,10,11,12,13,14,15,16,]
 
  - 
    - MCU-J11: [1,2,3,4,5,6,7,8,9,10,11,12,13,14,15,16,]
    - W2: [1,2,3,4,5,6,7,8,9,10,11,12,13,14,15,16,]
    - Panel-J2: [1,2,3,4,5,6,7,8,9,10,11,12,13,14,15,16,]
